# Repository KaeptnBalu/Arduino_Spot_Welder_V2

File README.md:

# Arduino_Spot_Welder_V2

This is the older V2 Version of the Arduino Spot Welder. The new V3 can be found here https://github.com/KaeptnBalu/Arduino_Spot_Welder_V3 The previous V1 can be found here https://github.com/KaeptnBalu/Arduino_Spot_Welder

An Arduino based Spot Welder for battery welding http://www.instructables.com/id/DIY-Arduino-Battery-Spot-Welder/ <br>
Build Video: https://www.youtube.com/watch?v=4qOaeutVR8I

3D prinable cases: 
- https://www.thingiverse.com/thing:2488481   (Thanks to Neil Paisnel)
- https://www.thingiverse.com/thing:2346476   (Thanks to AugustRetroDoom)

Improvements in the V2:

    - only one mosfet driver instead of four
    - changed electrolytic capacitor to film capacitor
    - capacitors closer to the mosfet driver
    - wider pcb traces for high current paths
    - added gate resistors for the mosfets
    - aluminum u-shaped part for the mosfet board (much easier to assemble)
    - general pcb layout improvements
    - pcb is now designed in KiCad (more open source than Eagle)
    
 Improvements in the V2.2:

    - Mosfet PCB now with 2oz copper layer and wider traces 
    which connect the high current carrying mosfet legs to the u-shaped aluminum part
    - little bit bigger mounting holes for u-shaped aluminum piece (2.6mm instead of 2.5mm)
    - "AutoPulse" feature, which automatically activates a pulse after a 2 second delay 
    when both welding tips touch the nickel strip (thanks to Petr Zverina for the idea)

This Spot Welder can be used to weld 18650 batteries. It needs a 7-12V power source (12V recommended) and uses a 12V car battery as welding current supply. Typically one 45Ah battery delivers enough current to get good welds with 0.15mm nickel strips. For thicker nickel strips maybe you will need bigger battery or two in paralell.

The Welder generates a double pulse, where the first one is 1/8 of the time of the second one. Pulse time of second pulse is adjustable by the potentiometer and displayed on the screen in mS so you can exactly adjust the time. Its adjustable from 1 ... 90 mS.

If you want to download the project click on "clone or download" on this page. Downloading single files sometimes seems to cause some files to be corrupted while downloading.

You can get parts to build your own Spot Welder or prebuilt kits at https://malectrics.eu/

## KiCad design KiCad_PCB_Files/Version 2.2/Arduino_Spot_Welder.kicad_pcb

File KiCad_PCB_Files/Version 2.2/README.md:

Improvements in Version 2.2

- Mosfet PCB now with 2oz copper layer and wider traces which connect the high current carrying mosfet legs to the u-shaped aluminum part
- little bit bigger mounting holes for u-shaped aluminum piece (2.6mm instead of 2.5mm)
- "AutoPulse" feature, which automatically activates a pulse after a 2 second delay when both welding tips touch the nickel strip (thanks to Petr Zverina for the idea)

The mosfet pcb update was done because some users who tryed welding with more than 1000A current reported that the pcb traces got damaged by the high current. Now it should be more resistant even to these very high currents.

The new "AutoPulse" feature only needs 5 small additional parts on the pcb. (470 Ohm resistor, 620 Ohm resistor, z-diode 4,3V 0,5w, 2,54mm jumper, 2 pin 2,54mm male header). Resistor R13 does not need to be populated. It was meant as a pull down resistor, but after looking close to the schematic i realised R14 + R15 already do the pull down to GND.

To activate the "AutoPulse" feature simply plug a jumper on the male 2 pin header named "Auto_Pulse" which connects the two pins.

You can get the new V2.2 PCB Sets here: https://malectrics.eu/

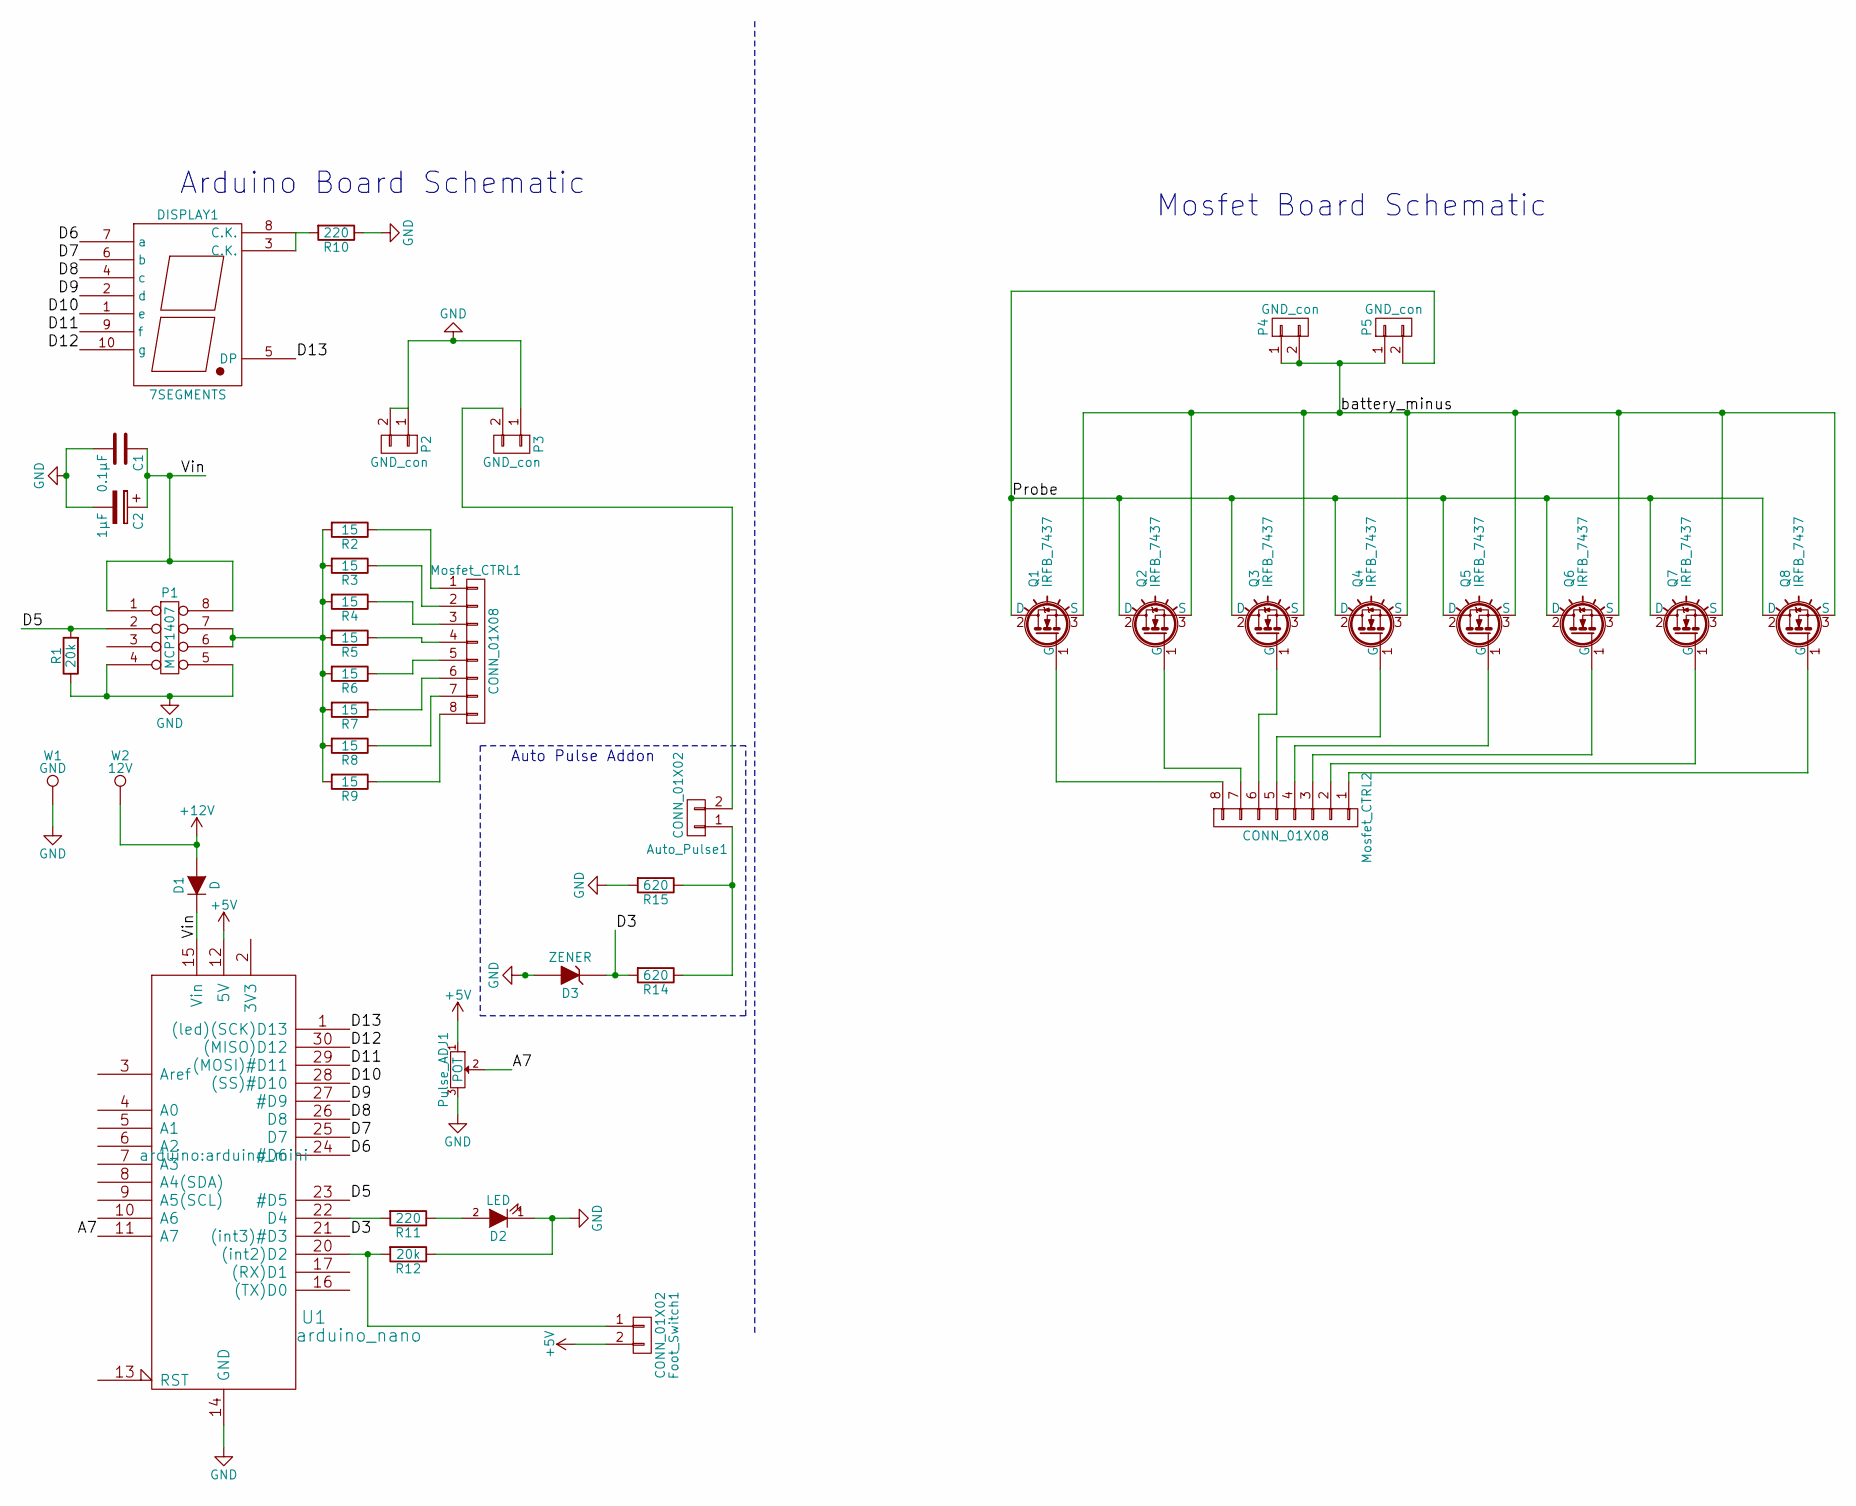
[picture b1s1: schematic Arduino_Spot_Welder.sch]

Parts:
Auto_Pulse1: CONN_01X02; Pin_Header_Straight_1x02_Pitch2.54mm
C1: 0.1µF; C_1210_HandSoldering
C2: 1µF; C_Disc_D7.5mm_W5.0mm_P5.00mm
D1: D; D_SMA_Handsoldering
D2: LED; R_1206_HandSoldering
D3: ZENER; D_MiniMELF_Handsoldering
DISPLAY1: 7SEGMENTS; 7SegmentLED_LTS6760_LTS6780
Foot_Switch1: CONN_01X02; Molex_KK-6410-02_02x2.54mm_Straight
Mosfet_CTRL1, Mosfet_CTRL2: CONN_01X08; Pin_Header_Straight_1x08_Pitch2.54mm_Large_Pads
P1: MCP1407; DIP-8_W7.62mm_Socket_LongPads
P2, P3, P4, P5: GND_con; Pin_Header_Straight_1x02_Pitch2.54mm
Pulse_ADJ1: POT; RK09K1130A5R
Q1, Q2, Q3, Q4, Q5, Q6, Q7, Q8: IRFB_7437; TO-220__long_Neutral123_Horizontal_LargePads
R1, R12: 20k; R_1206_HandSoldering
R2, R3, R4, R5, R6, R7, R8, R9: 15; R_1206_HandSoldering
R10, R11: 220; R_1206_HandSoldering
R14, R15: 620; R_1206_HandSoldering
U1: arduino_nano; arduino_mini
W1: GND; SolderWirePad_single_1mmDrill
W2: 12V; SolderWirePad_single_1mmDrill

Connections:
+5V: Foot_Switch1.2, Pulse_ADJ1.1, U1.12 (5V); also elsewhere on the board
+12V: D1.2 (A), W2.1
/A7: Pulse_ADJ1.2, U1.11 (A7); also elsewhere on the board
/D3: D3.1 (K), R14.2, U1.21 ((int3)#D3)
/D5: P1.2, R1.2, U1.23 (#D5)
/D6: DISPLAY1.7 (a), U1.24 (#D6); also elsewhere on the board
/D7: DISPLAY1.6 (b), U1.25 (D7); also elsewhere on the board
/D8: DISPLAY1.4 (c), U1.26 (D8); also elsewhere on the board
/D9: DISPLAY1.2 (d), U1.27 (#D9); also elsewhere on the board
/D10: DISPLAY1.1 (e), U1.28 ((SS)#D10); also elsewhere on the board
/D11: DISPLAY1.9 (f), U1.29 ((MOSI)#D11); also elsewhere on the board
/D12: DISPLAY1.10 (g), U1.30 ((MISO)D12); also elsewhere on the board
/D13: DISPLAY1.5 (DP), U1.1 ((led)(SCK)D13); also elsewhere on the board
/Probe: P5.2, Q1.2 (D), Q2.2 (D), Q3.2 (D), Q4.2 (D), Q5.2 (D), Q6.2 (D), Q7.2 (D), Q8.2 (D)
/Vin: C1.1, C2.1, D1.1 (K), P1.1, P1.8, U1.15 (Vin)
/battery_minus: P4.1, P4.2, P5.1, Q1.3 (S), Q2.3 (S), Q3.3 (S), Q4.3 (S), Q5.3 (S), Q6.3 (S), Q7.3 (S), Q8.3 (S)
GND: C1.2, C2.2, D2.1 (K), D3.2 (A), P1.4, P1.5, P2.1, P2.2, P3.1, Pulse_ADJ1.3, R1.1, R10.1, R12.1, R15.2, U1.14 (GND), U1.19 (GND), W1.1; also elsewhere on the board
unnamed 17: Auto_Pulse1.1, R14.1, R15.1; also elsewhere on the board
unnamed 18: Auto_Pulse1.2, P3.2; also elsewhere on the board
unnamed: D2.2 (A), R11.1
unnamed 20: DISPLAY1.3 (C.K.), DISPLAY1.8 (C.K.), R10.2; also elsewhere on the board
unnamed 21: Foot_Switch1.1, R12.2, U1.20 ((int2)D2); also elsewhere on the board
unnamed: Mosfet_CTRL1.1, R2.1
unnamed: Mosfet_CTRL1.2, R3.1
unnamed: Mosfet_CTRL1.3, R4.1
unnamed: Mosfet_CTRL1.4, R5.1
unnamed: Mosfet_CTRL1.5, R6.1
unnamed: Mosfet_CTRL1.6, R7.1
unnamed: Mosfet_CTRL1.7, R8.1
unnamed: Mosfet_CTRL1.8, R9.1
unnamed: Mosfet_CTRL2.1, Q8.1 (G)
unnamed: Mosfet_CTRL2.2, Q7.1 (G)
unnamed: Mosfet_CTRL2.3, Q6.1 (G)
unnamed: Mosfet_CTRL2.4, Q5.1 (G)
unnamed: Mosfet_CTRL2.5, Q4.1 (G)
unnamed: Mosfet_CTRL2.6, Q3.1 (G)
unnamed: Mosfet_CTRL2.7, Q2.1 (G)
unnamed: Mosfet_CTRL2.8, Q1.1 (G)
unnamed: P1.6, P1.7, R2.2, R3.2, R4.2, R5.2, R6.2, R7.2, R8.2, R9.2
unnamed: R11.2, U1.22 (D4)

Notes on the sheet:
Arduino Board Schematic
Mosfet Board Schematic
Auto Pulse Addon

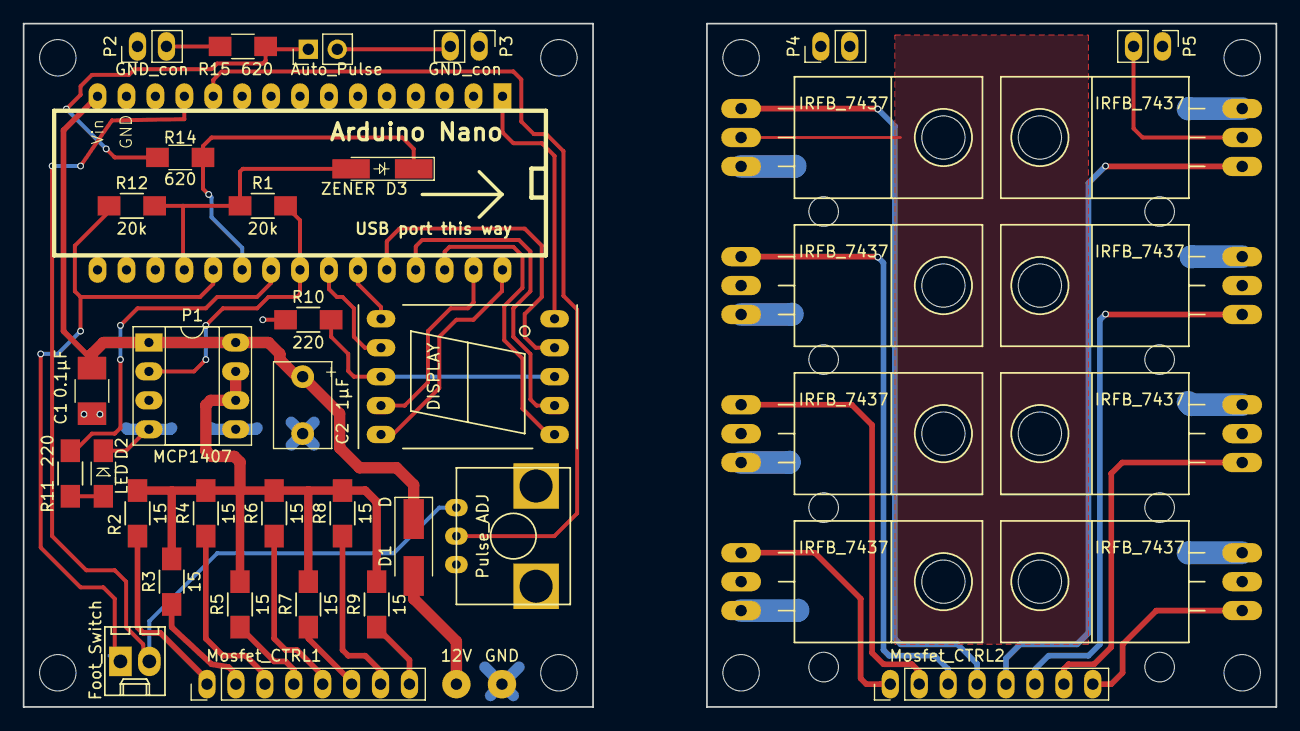
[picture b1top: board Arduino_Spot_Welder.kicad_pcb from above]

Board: 2 copper layers, 110.0 x 60.0 mm, 41 parts (0 on the bottom side), 40 nets.

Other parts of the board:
Auto_Pulse: Jumper; Pin_Header_Straight_1x02_Pitch2.54mm
DISPLAY: 7SEGMENTS; 7SegmentLED_LTS6760_LTS6780
Foot_Switch: CONN_01X02; Molex_KK-6410-02_02x2.54mm_Straight
Pulse_ADJ: POT; RK09K1130A5R

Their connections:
+5V: Foot_Switch.2, Pulse_ADJ.1; also elsewhere on the board
/A7: Pulse_ADJ.2; also elsewhere on the board
/D6: DISPLAY.7; also elsewhere on the board
/D7: DISPLAY.6; also elsewhere on the board
/D8: DISPLAY.4; also elsewhere on the board
/D9: DISPLAY.2; also elsewhere on the board
/D10: DISPLAY.1; also elsewhere on the board
/D11: DISPLAY.9; also elsewhere on the board
/D12: DISPLAY.10; also elsewhere on the board
/D13: DISPLAY.5; also elsewhere on the board
GND: Pulse_ADJ.3; also elsewhere on the board
unnamed 17: Auto_Pulse.1; also elsewhere on the board
unnamed 18: Auto_Pulse.2; also elsewhere on the board
unnamed 20: DISPLAY.3, DISPLAY.8; also elsewhere on the board
unnamed 21: Foot_Switch.1; also elsewhere on the board

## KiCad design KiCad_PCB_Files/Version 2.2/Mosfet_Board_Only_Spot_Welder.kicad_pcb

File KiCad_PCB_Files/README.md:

The spot welder is made of two boards which are stacked on top of each other.
One board contains all the logic and low power electronic components and the other one contains the Mosfets.

The gerber files are made to be used at pcbway.com 
You can support me by registering through this link http://www.pcbway.com/setinvite.aspx?inviteid=12824
This way you get a 5$ coupon for your order and i get some percent discount at the shop for upcoming projects.

As the Gerber Files you can use the Spot_Welder_V2_Gerber.zip or the latest Spot_Welder_V2.1_Gerber.zip which have both boards combined to one big board. 
You have to cut this in half at home to get the two single boards.

To download the files please download the complete project by clicking on the "clone or download" button on the projects main page (https://github.com/KaeptnBalu/Arduino_Spot_Welder_V2)
Downloading by right click and "save as" does seem to cause problems.

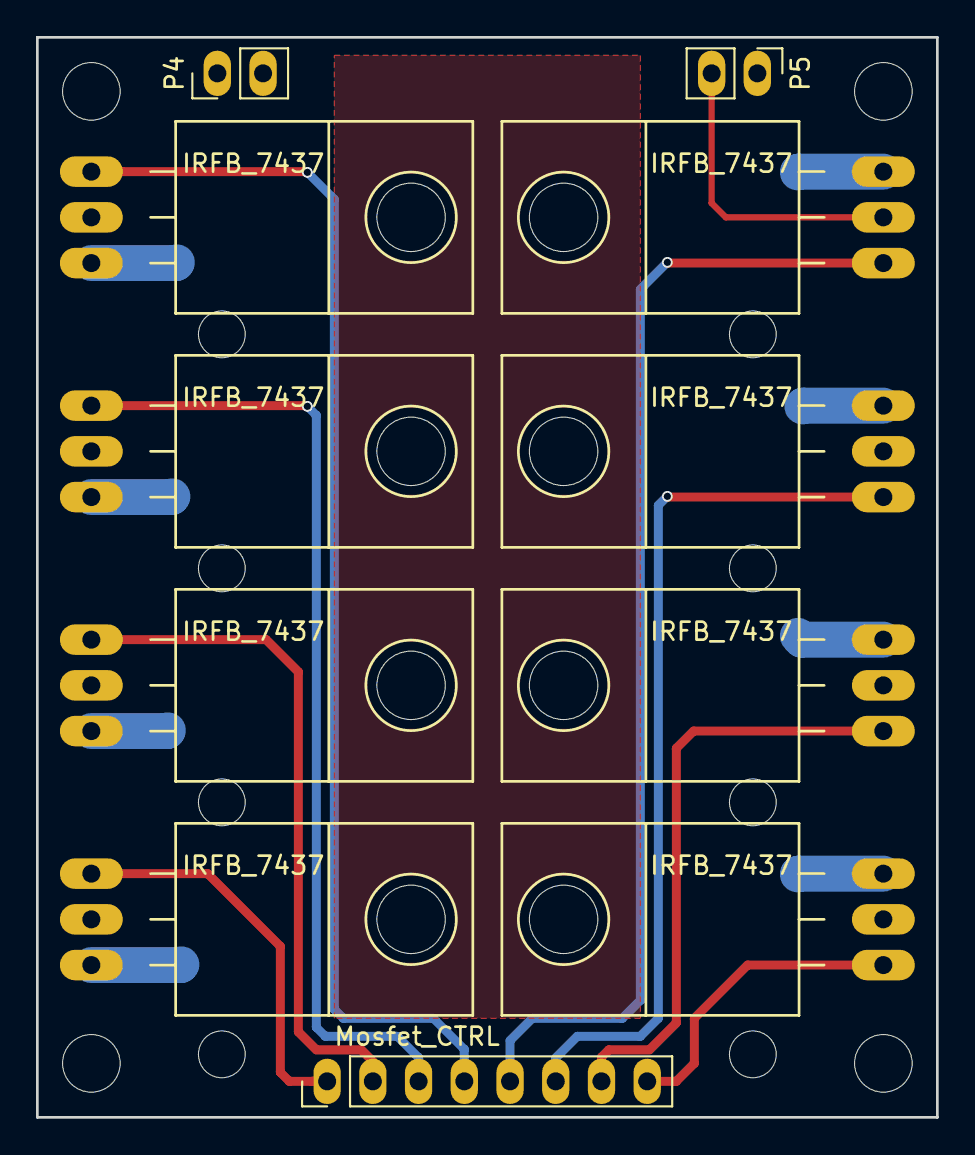
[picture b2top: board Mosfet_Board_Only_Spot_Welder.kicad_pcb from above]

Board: 2 copper layers, 50.0 x 60.0 mm, 11 parts (0 on the bottom side), 10 nets.

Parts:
Mosfet_CTRL: CONN_01X08; Pin_Header_Straight_1x08_Pitch2.54mm_Large_Pads
P4, P5: GND_con; Pin_Header_Straight_1x02_Pitch2.54mm
Q1, Q2, Q3, Q4, Q5, Q6, Q7, Q8: IRFB_7437; TO-220__long_Neutral123_Horizontal_LargePads

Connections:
/Probe: P5.2, Q1.2, Q2.2, Q3.2, Q4.2, Q5.2, Q6.2, Q7.2, Q8.2
/battery_minus: P4.1, P4.2, P5.1, Q1.3, Q2.3, Q3.3, Q4.3, Q5.3, Q6.3, Q7.3, Q8.3
unnamed: Mosfet_CTRL.1, Q8.1
unnamed: Mosfet_CTRL.2, Q7.1
unnamed: Mosfet_CTRL.3, Q6.1
unnamed: Mosfet_CTRL.4, Q5.1
unnamed: Mosfet_CTRL.5, Q4.1
unnamed: Mosfet_CTRL.6, Q3.1
unnamed: Mosfet_CTRL.7, Q2.1
unnamed: Mosfet_CTRL.8, Q1.1

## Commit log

2017-03-08 Create Aluminum_Parts
2017-03-08 bill of material
2017-04-05 Rename Reichelt.de_shopping_cart to Reichelt.de_shopping_cart_V2
2017-04-05 Shopping Cart for Version 2
2017-05-13 updated film capacitor
2017-05-18 added AutoPulse feature
2017-06-03 updated mosfets
2017-06-09 removed R13
2017-06-09 changed mosfets to IRFB7437
2017-06-24 default max pulse time now 90mS
2017-07-16 Changed R15 to 470 Ohm
2017-07-20 Alternative to Reichelt V2.2 shopping cart
